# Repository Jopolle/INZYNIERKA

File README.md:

# Repozytorium projektu inżynierskiego

W repozytorium znajdują się wszystkie istotne pliki dotyczące projektu

- Folder HVAC_STM32F7_PCB zawiera schematy projektowanego PCB jak i projekt samej płytki

- Folder dokumentacja zawiera pliki LaTeX pracy inżynierskiej i ostatnią skompilowaną wersję

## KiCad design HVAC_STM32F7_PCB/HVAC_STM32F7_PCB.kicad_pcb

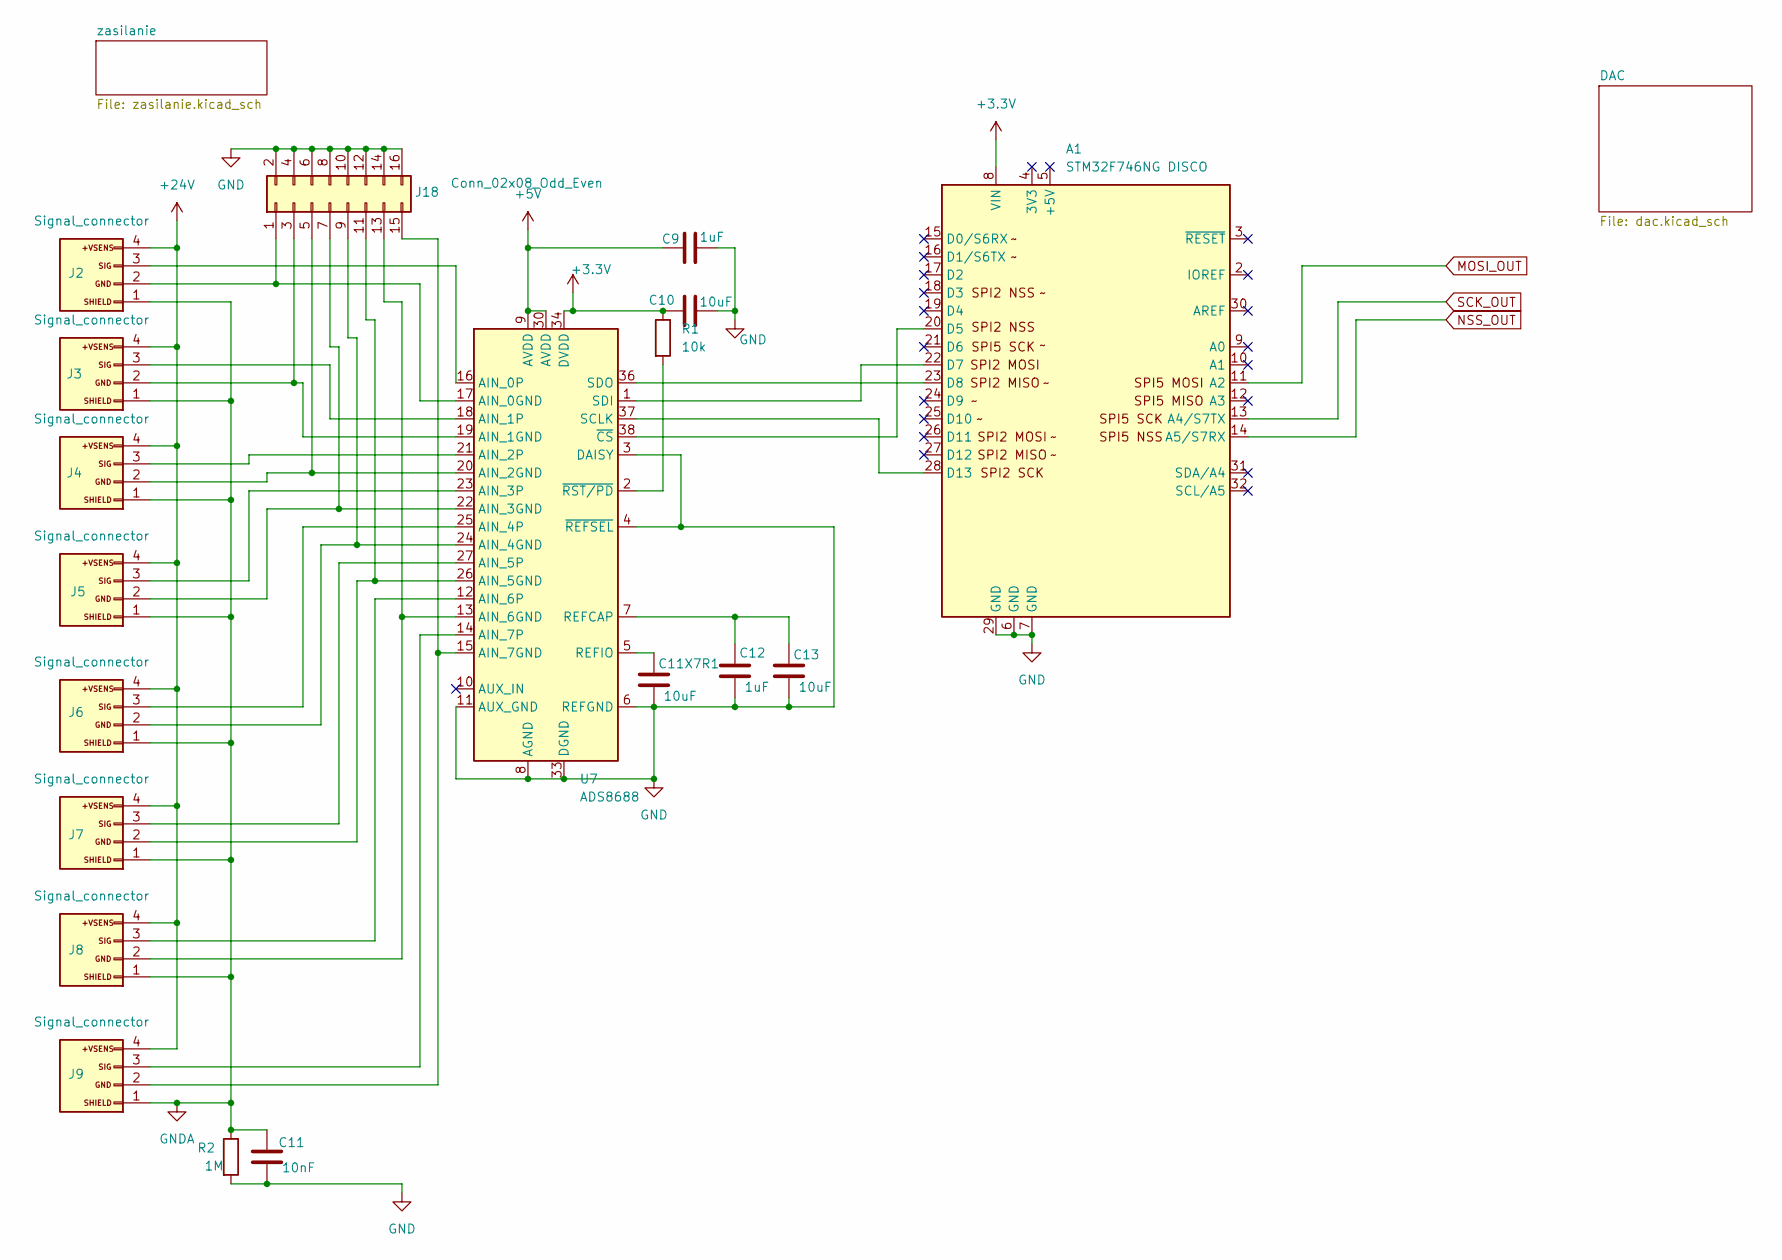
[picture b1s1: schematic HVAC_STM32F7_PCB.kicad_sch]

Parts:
A1: STM32F746NG DISCO; STM32F7_DISCO
C9, C12: 1uF; C_0805_2012Metric_Pad1.18x1.45mm_HandSolder
C10, C11X7R1, C13: 10uF; C_0805_2012Metric_Pad1.18x1.45mm_HandSolder
C11: 10nF; C_0805_2012Metric_Pad1.18x1.45mm_HandSolder
J2, J3, J4, J5, J6, J7, J8, J9: Signal_connector; PhoenixContact_MCV_1,5_4-G-3.5_1x04_P3.50mm_Vertical
J18: Conn_02x08_Odd_Even; PinHeader_2x08_P2.54mm_Vertical
R1: 10k; R_0805_2012Metric_Pad1.20x1.40mm_HandSolder
R2: 1M; R_0805_2012Metric_Pad1.20x1.40mm_HandSolder
U7: ADS8688; TSSOP-38_4.4x9.7mm_P0.5mm

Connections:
+3.3V: A1.8 (VIN), C10.1, R1.1, U7.34 (DVDD); also elsewhere on the board
+5V: C9.2, U7.9 (AVDD), U7.30 (AVDD); also elsewhere on the board
+24V: J2.4 (+VSENS), J3.4 (+VSENS), J4.4 (+VSENS), J5.4 (+VSENS), J6.4 (+VSENS), J7.4 (+VSENS), J8.4 (+VSENS), J9.4 (+VSENS); also elsewhere on the board
GND: A1.6 (GND), A1.7 (GND), A1.29 (GND), C9.1, C10.2, C11.2, C11X7R1.2, C12.2, C13.2, J18.2, J18.4, J18.6, J18.8, J18.10, J18.12, J18.14, J18.16, R2.2, U7.3 (DAISY), U7.4 (~REFSEL), U7.6 (REFGND), U7.8 (AGND), U7.11 (AUX_GND), U7.28 (AGND), U7.29 (AGND), U7.31 (AGND), U7.32 (AGND), U7.33 (DGND); also elsewhere on the board
GNDA: C11.1, J2.1 (SHIELD), J3.1 (SHIELD), J4.1 (SHIELD), J5.1 (SHIELD), J6.1 (SHIELD), J7.1 (SHIELD), J8.1 (SHIELD), J9.1 (SHIELD), R2.1; also elsewhere on the board
MOSI_OUT: A1.11 (A2); also elsewhere on the board
NSS_OUT: A1.14 (A5/S7RX); also elsewhere on the board
unnamed: A1.20 (D5), U7.38 (~CS)
unnamed: A1.22 (D7), U7.1 (SDI)
unnamed: A1.23 (D8), U7.36 (SDO)
unnamed: A1.28 (D13), U7.37 (SCLK)
unnamed: J2.3 (SIG), U7.16 (AIN_0P)
unnamed: J3.3 (SIG), U7.18 (AIN_1P)
unnamed: J4.3 (SIG), U7.21 (AIN_2P)
unnamed: J5.3 (SIG), U7.23 (AIN_3P)
unnamed: J6.3 (SIG), U7.25 (AIN_4P)
unnamed: J7.3 (SIG), U7.27 (AIN_5P)
unnamed: J8.3 (SIG), U7.12 (AIN_6P)
unnamed: J9.3 (SIG), U7.14 (AIN_7P)
unnamed: J2.2 (GND), J18.1, U7.17 (AIN_0GND)
unnamed: J3.2 (GND), J18.3, U7.19 (AIN_1GND)
unnamed: J4.2 (GND), J18.5, U7.20 (AIN_2GND)
unnamed: J5.2 (GND), J18.7, U7.22 (AIN_3GND)
unnamed: J6.2 (GND), J18.9, U7.24 (AIN_4GND)
unnamed: J7.2 (GND), J18.11, U7.26 (AIN_5GND)
unnamed: J8.2 (GND), J18.13, U7.13 (AIN_6GND)
unnamed: J9.2 (GND), J18.15, U7.15 (AIN_7GND)
unnamed: C12.1, C13.1, U7.7 (REFCAP)
unnamed: C11X7R1.1, U7.5 (REFIO)
unnamed: R1.2, U7.2 (~RST/PD)
SCK_OUT: A1.13 (A4/S7TX); also elsewhere on the board

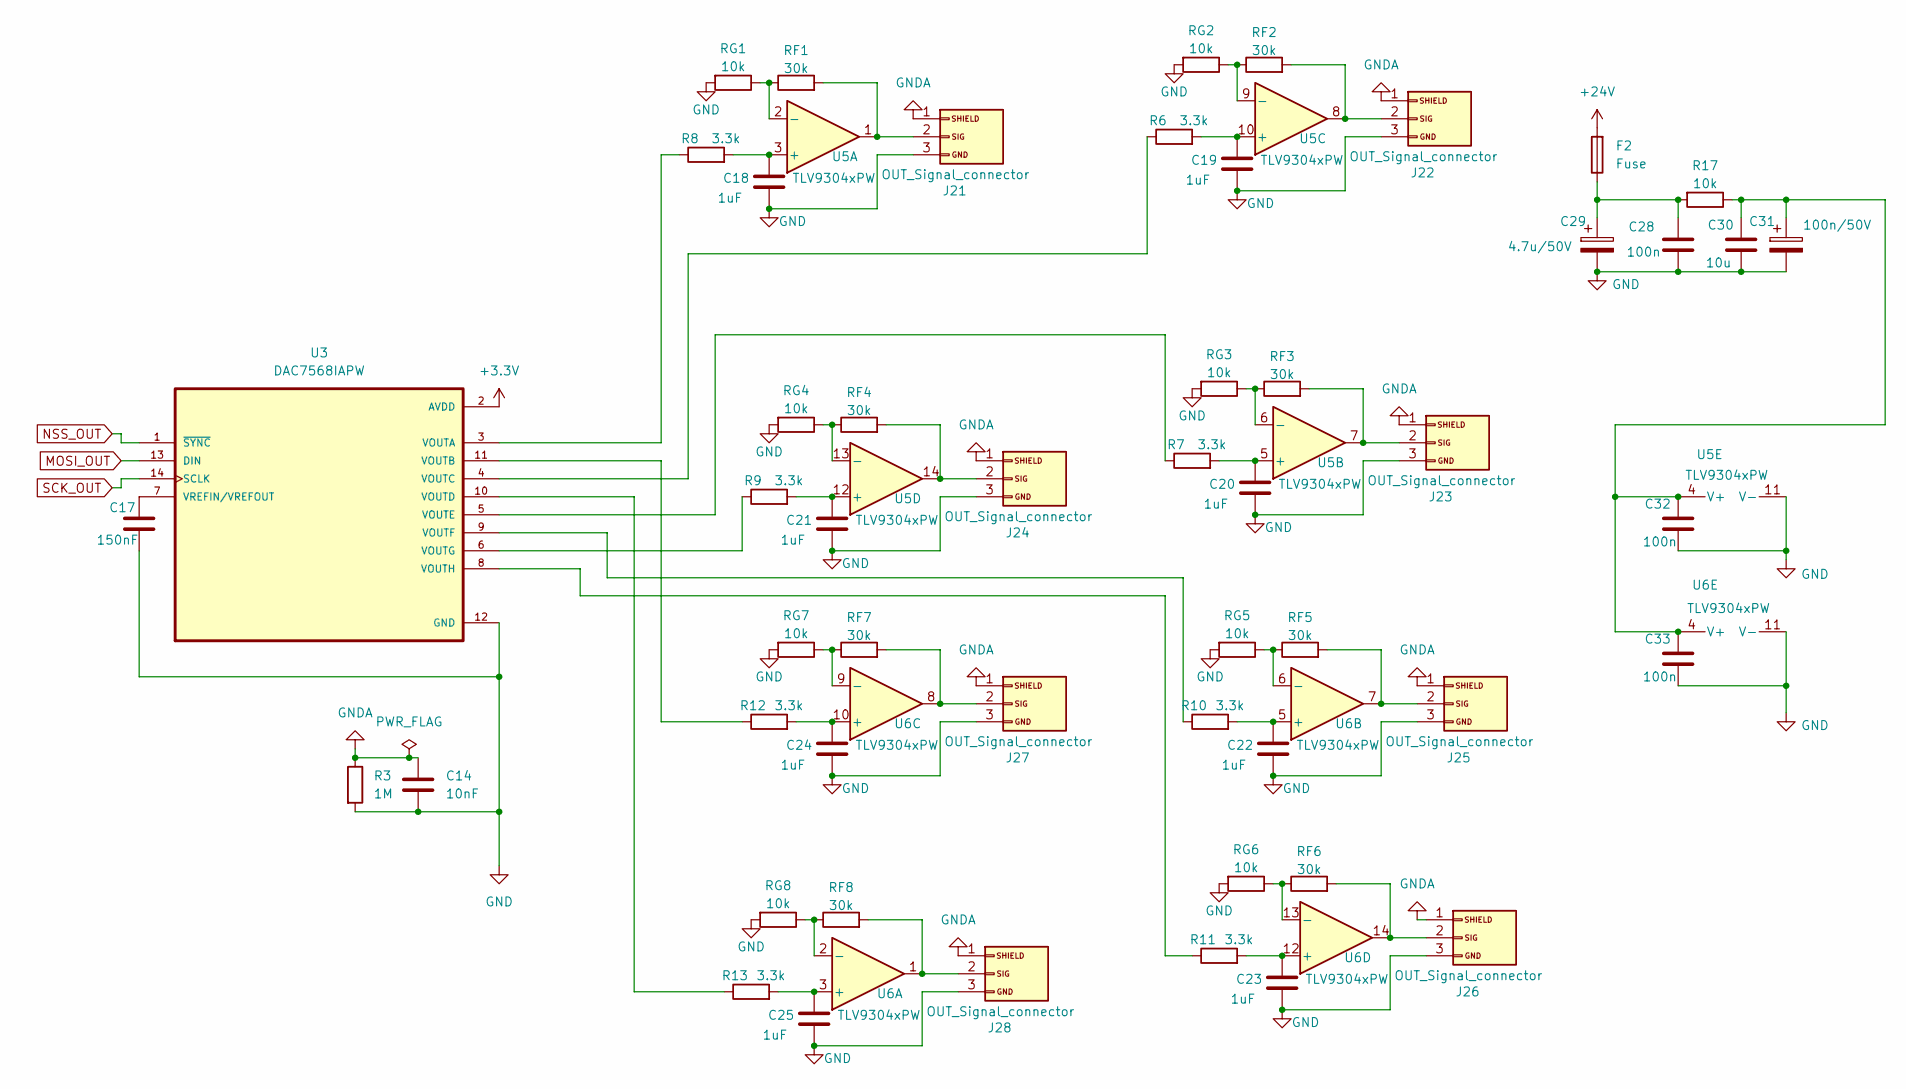
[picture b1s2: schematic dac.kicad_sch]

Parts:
C14: 10nF; C_0805_2012Metric_Pad1.18x1.45mm_HandSolder
C17: 150nF; C_0805_2012Metric_Pad1.18x1.45mm_HandSolder
C18, C19, C20, C21, C22, C23, C24, C25: 1uF; C_0805_2012Metric_Pad1.18x1.45mm_HandSolder
C28, C32, C33: 100n; C_0805_2012Metric_Pad1.18x1.45mm_HandSolder
C29: 4.7u/50V; C_2220_5750Metric_Pad1.97x5.40mm_HandSolder
C30: 10u; C_0805_2012Metric_Pad1.18x1.45mm_HandSolder
C31: 100n/50V; C_0805_2012Metric_Pad1.18x1.45mm_HandSolder
F2: Fuse; Fuse_1812_4532Metric_Pad1.30x3.40mm_HandSolder
J21, J22, J23, J24, J25, J26, J27, J28: OUT_Signal_connector; PhoenixContact_MCV_1,5_3-G-3.5_1x03_P3.50mm_Vertical
R3: 1M; R_0805_2012Metric_Pad1.20x1.40mm_HandSolder
R6, R7, R8, R9, R10, R11, R12, R13: 3.3k; R_0805_2012Metric_Pad1.20x1.40mm_HandSolder
R17: 10k; R_0805_2012Metric_Pad1.20x1.40mm_HandSolder
RF1, RF2, RF3, RF4, RF5, RF6, RF7, RF8: 30k; R_0805_2012Metric_Pad1.20x1.40mm_HandSolder
RG1, RG2, RG3, RG4, RG5, RG6, RG7, RG8: 10k; R_0805_2012Metric_Pad1.20x1.40mm_HandSolder
U3: DAC7568IAPW; dac
U5, U6: TLV9304xPW; TSSOP-14_4.4x5mm_P0.65mm

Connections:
+3.3V: U3.2 (AVDD); also elsewhere on the board
+24V: F2.2; also elsewhere on the board
GND: C14.2, C17.2, C18.2, C19.2, C20.2, C21.2, C22.2, C23.2, C24.2, C25.2, C28.2, C29.2, C30.2, C31.2, C32.2, C33.2, J21.3 (SIG), J22.3 (SIG), J23.3 (SIG), J24.3 (SIG), J25.3 (SIG), J26.3 (SIG), J27.3 (SIG), J28.3 (SIG), R3.2, RG1.2, RG2.2, RG3.2, RG4.2, RG5.2, RG6.2, RG7.2, RG8.2, U3.12 (GND), U5.11 (V-), U6.11 (V-); also elsewhere on the board
GNDA: C14.1, J21.1 (SHIELD), J22.1 (SHIELD), J23.1 (SHIELD), J24.1 (SHIELD), J25.1 (SHIELD), J26.1 (SHIELD), J27.1 (SHIELD), J28.1 (SHIELD), R3.1; also elsewhere on the board
MOSI_OUT: U3.13 (DIN); also elsewhere on the board
NSS_OUT: U3.1 (~SYNC); also elsewhere on the board
unnamed: C28.1, C29.1, F2.1, R17.2
unnamed: J21.2 (GND), RF1.2, U5.1
unnamed: J22.2 (GND), RF2.2, U5.8
unnamed: J23.2 (GND), RF3.2, U5.7
unnamed: J24.2 (GND), RF4.2, U5.14
unnamed: J25.2 (GND), RF5.2, U6.7
unnamed: J26.2 (GND), RF6.2, U6.14
unnamed: J27.2 (GND), RF7.2, U6.8
unnamed: J28.2 (GND), RF8.2, U6.1
unnamed: R8.1, U3.3 (VOUTA)
unnamed: R12.1, U3.11 (VOUTB)
unnamed: R6.1, U3.4 (VOUTC)
unnamed: R13.1, U3.10 (VOUTD)
unnamed: R7.1, U3.5 (VOUTE)
unnamed: R10.1, U3.9 (VOUTF)
unnamed: R9.1, U3.6 (VOUTG)
unnamed: R11.1, U3.8 (VOUTH)
unnamed: C17.1, U3.7 (VREFIN/VREFOUT)
unnamed: C18.1, R8.2, U5.3 (+)
unnamed: RF1.1, RG1.1, U5.2 (-)
unnamed: C20.1, R7.2, U5.5 (+)
unnamed: RF3.1, RG3.1, U5.6 (-)
unnamed: C19.1, R6.2, U5.10 (+)
unnamed: RF2.1, RG2.1, U5.9 (-)
unnamed: C21.1, R9.2, U5.12 (+)
unnamed: RF4.1, RG4.1, U5.13 (-)
unnamed: C30.1, C31.1, C32.1, C33.1, R17.1, U5.4 (V+), U6.4 (V+)
unnamed: C25.1, R13.2, U6.3 (+)
unnamed: RF8.1, RG8.1, U6.2 (-)
unnamed: C22.1, R10.2, U6.5 (+)
unnamed: RF5.1, RG5.1, U6.6 (-)
unnamed: C24.1, R12.2, U6.10 (+)
unnamed: RF7.1, RG7.1, U6.9 (-)
unnamed: C23.1, R11.2, U6.12 (+)
unnamed: RF6.1, RG6.1, U6.13 (-)
SCK_OUT: U3.14 (SCLK); also elsewhere on the board

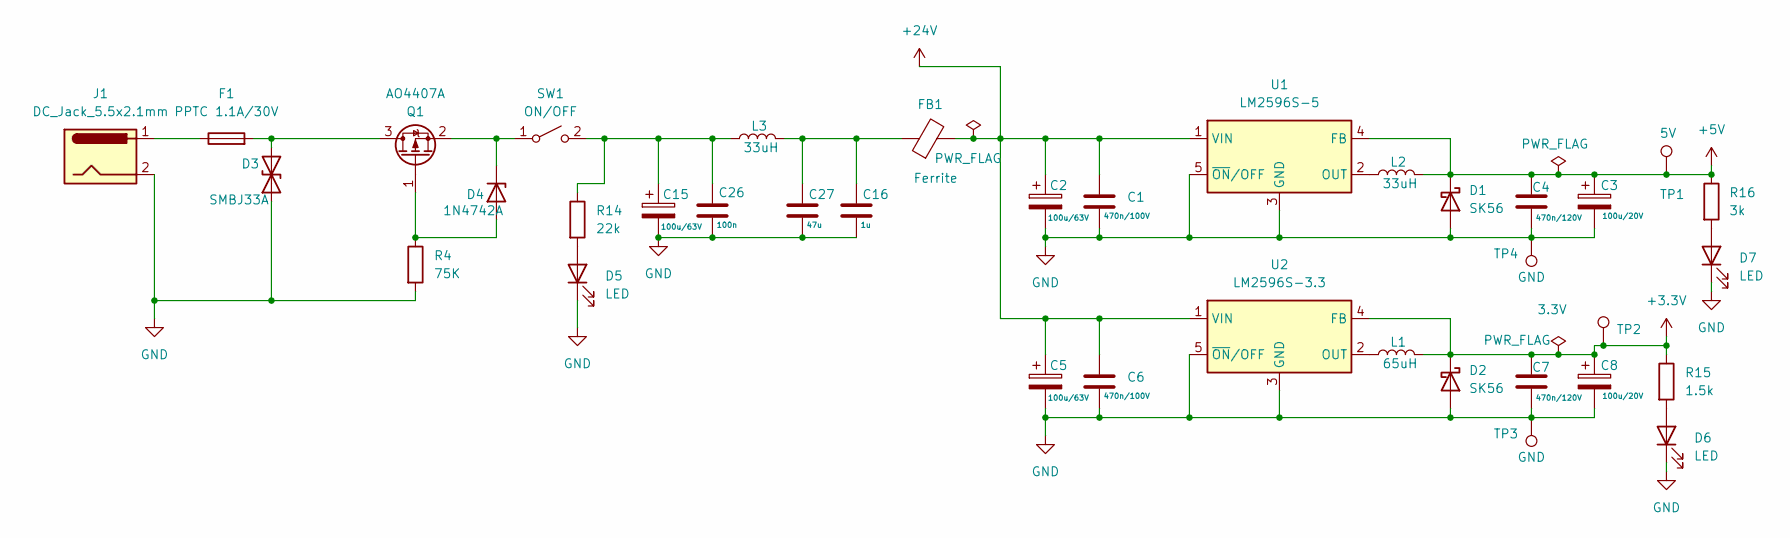
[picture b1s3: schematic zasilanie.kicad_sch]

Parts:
C1, C6: 470n/100V; C_1808_4520Metric_Pad1.72x2.30mm_HandSolder
C2, C5, C15: 100u/63V; CP_Radial_D8.0mm_P3.80mm
C3, C8: 100u/20V; CP_Radial_D8.0mm_P3.80mm
C4, C7: 470n/120V; C_1808_4520Metric_Pad1.72x2.30mm_HandSolder
C16: 1u; C_1808_4520Metric_Pad1.72x2.30mm_HandSolder
C26: 100n; C_1808_4520Metric_Pad1.72x2.30mm_HandSolder
C27: 47u; C_1808_4520Metric_Pad1.72x2.30mm_HandSolder
D1, D2: SK56; D_SMB-SMC_Universal_Handsoldering
D3: SMBJ33A; D_SMB_Handsoldering
D4: 1N4742A; D_DO-41_SOD81_P2.54mm_Vertical_AnodeUp
D5, D6, D7: LED; LED_D5.0mm_Clear
F1: PPTC 1.1A/30V; Fuseholder_Blade_Mini_Keystone_3568
FB1: Ferrite; L_1210_3225Metric_Pad1.42x2.65mm_HandSolder
J1: DC_Jack_5.5x2.1mm; BarrelJack_Horizontal
L1: 65uH; L_12x12mm_H4.5mm
L2, L3: 33uH; L_6.3x6.3_H3
Q1: AO4407A; PowerPAK_SO-8_Single
R4: 75K; R_0805_2012Metric_Pad1.20x1.40mm_HandSolder
R14: 22k; R_0805_2012Metric_Pad1.20x1.40mm_HandSolder
R15: 1.5k; R_0805_2012Metric_Pad1.20x1.40mm_HandSolder
R16: 3k; R_0805_2012Metric_Pad1.20x1.40mm_HandSolder
SW1: ON/OFF; SLW-1276864-4A-D_FOOTPRINT
TP1: 5V; TestPoint_Loop_D1.80mm_Drill1.0mm_Beaded
TP2: 3.3V; TestPoint_Loop_D1.80mm_Drill1.0mm_Beaded
TP3, TP4: GND; TestPoint_Loop_D1.80mm_Drill1.0mm_Beaded
U1: LM2596S-5; TO-263-5_TabPin3
U2: LM2596S-3.3; TO-263-5_TabPin3

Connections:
+3.3V: C7.1, C8.1, D2.1 (K), L1.2, R15.1, TP2.1, U2.4 (FB); also elsewhere on the board
+5V: C3.1, C4.1, D1.1 (K), L2.2, R16.1, TP1.1, U1.4 (FB); also elsewhere on the board
+24V: C1.1, C2.1, C5.1, C6.1, FB1.2, U1.1 (VIN), U2.1 (VIN); also elsewhere on the board
GND: C1.2, C2.2, C3.2, C4.2, C5.2, C6.2, C7.2, C8.2, C15.2, C16.2, C26.2, C27.2, D1.2 (A), D2.2 (A), D3.1 (A1), D5.1 (K), D6.1 (K), D7.1 (K), J1.2, R4.2, TP3.1, TP4.1, U1.3 (GND), U1.5 (~ON/OFF), U2.3 (GND), U2.5 (~ON/OFF); also elsewhere on the board
unnamed: C16.1, C27.1, FB1.1, L3.2
unnamed: D3.2 (A2), F1.2, Q1.3 (D)
unnamed: D4.2 (A), Q1.1 (G), R4.1
unnamed: D4.1 (K), Q1.2 (S), SW1.1 (A)
unnamed: D5.2 (A), R14.2
unnamed: D6.2 (A), R15.2
unnamed: D7.2 (A), R16.2
unnamed: F1.1, J1.1
unnamed: C15.1, C26.1, L3.1, R14.1, SW1.2 (B)
unnamed: L2.1, U1.2 (OUT)
unnamed: L1.1, U2.2 (OUT)

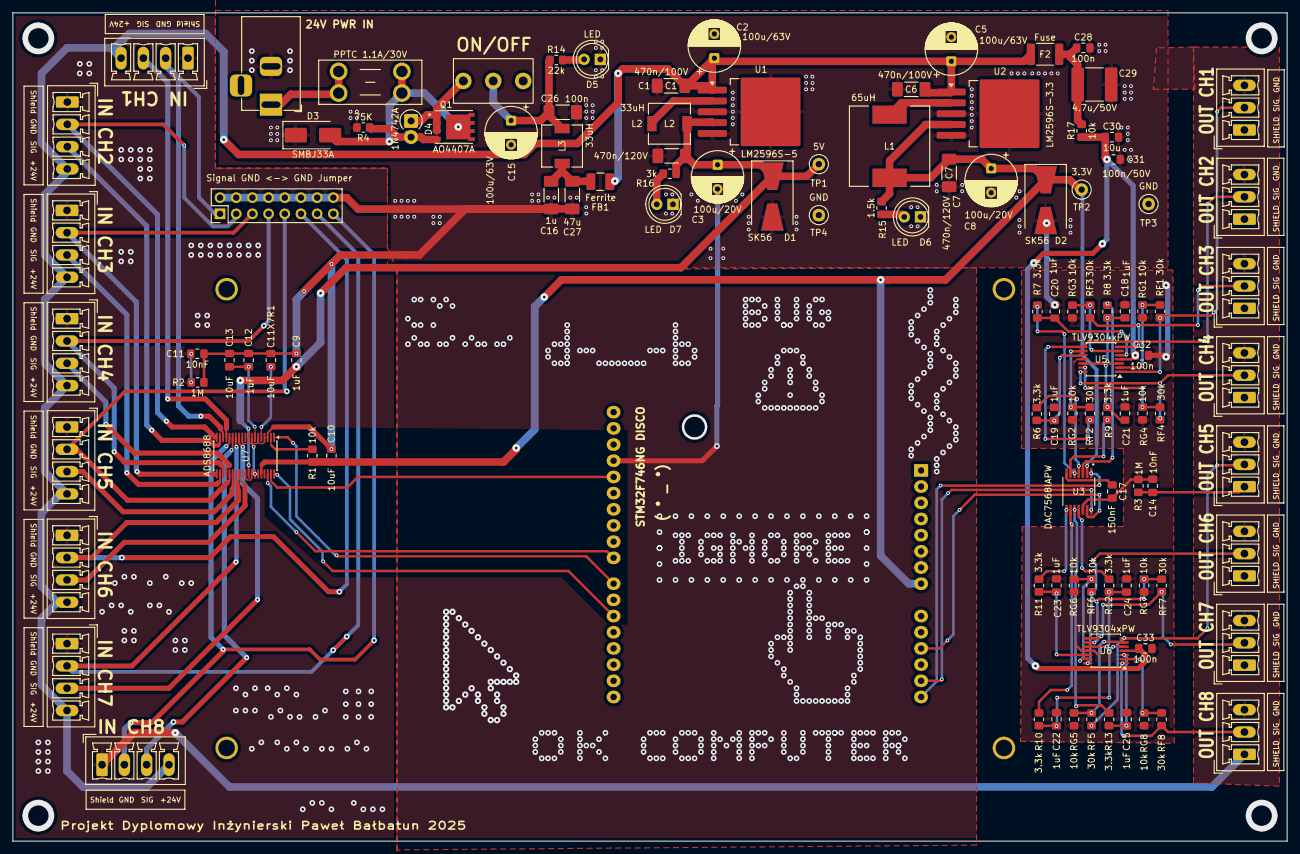
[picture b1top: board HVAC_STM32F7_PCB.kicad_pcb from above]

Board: 4 copper layers, 200.0 x 130.0 mm, 110 parts (0 on the bottom side), 77 nets.

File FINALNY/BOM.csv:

"Value","Footprint","Qty","Reference","DNP","Exclude from BOM","Exclude from Board","Datasheet"
"470n/100V","Capacitor_SMD:C_1808_4520Metric_Pad1.72x2.30mm_HandSolder","2","C1,C6","","","","~"
"100u/63V","Capacitor_THT:CP_Radial_D8.0mm_P3.80mm","3","C2,C5,C15","","","","~"
"100u/20V","Capacitor_THT:CP_Radial_D8.0mm_P3.80mm","2","C3,C8","","","","~"
"470n/120V","Capacitor_SMD:C_1808_4520Metric_Pad1.72x2.30mm_HandSolder","2","C4,C7","","","","~"
"1uF","Capacitor_SMD:C_0805_2012Metric_Pad1.18x1.45mm_HandSolder","10","C9,C12,C18,C19,C20,C21,C22,C23,C24,C25","","","","~"
"10uF","Capacitor_SMD:C_0805_2012Metric_Pad1.18x1.45mm_HandSolder","3","C10,C11X7R1,C13","","","","~"
"10nF","Capacitor_SMD:C_0805_2012Metric_Pad1.18x1.45mm_HandSolder","2","C11,C14","","","","~"
"1u","Capacitor_SMD:C_1808_4520Metric_Pad1.72x2.30mm_HandSolder","1","C16","","","","~"
"150nF","Capacitor_SMD:C_0805_2012Metric_Pad1.18x1.45mm_HandSolder","1","C17","","","","~"
"100n","Capacitor_SMD:C_1808_4520Metric_Pad1.72x2.30mm_HandSolder","1","C26","","","","~"
"47u","Capacitor_SMD:C_1808_4520Metric_Pad1.72x2.30mm_HandSolder","1","C27","","","","~"
"100n","Capacitor_SMD:C_0805_2012Metric_Pad1.18x1.45mm_HandSolder","3","C28,C32,C33","","","","~"
"4.7u/50V","Capacitor_SMD:C_2220_5750Metric_Pad1.97x5.40mm_HandSolder","1","C29","","","","~"
"10u","Capacitor_SMD:C_0805_2012Metric_Pad1.18x1.45mm_HandSolder","1","C30","","","","~"
"100n/50V","Capacitor_SMD:C_0805_2012Metric_Pad1.18x1.45mm_HandSolder","1","C31","","","","~"
"SK56","Diode_SMD:D_SMB-SMC_Universal_Handsoldering","2","D1,D2","","","","~"
"SMBJ33A","Diode_SMD:D_SMB_Handsoldering","1","D3","","","","~"
"1N4742A","Diode_THT:D_DO-41_SOD81_P2.54mm_Vertical_AnodeUp","1","D4","","","","~"
"LED","LED_THT:LED_D5.0mm_Clear","3","D5,D6,D7","","","","~"
"PPTC 1.1A/30V","Fuse:Fuseholder_Blade_Mini_Keystone_3568","1","F1","","","","~"
"Fuse","Fuse:Fuse_1812_4532Metric_Pad1.30x3.40mm_HandSolder","1","F2","","","","~"
"Ferrite","Inductor_SMD:L_1210_3225Metric_Pad1.42x2.65mm_HandSolder","1","FB1","","","","~"
"DC_Jack_5.5x2.1mm","Connector_BarrelJack:BarrelJack_Horizontal","1","J1","","","","~"
"Signal_connector","Connector_Phoenix_MC:PhoenixContact_MCV_1,5_4-G-3.5_1x04_P3.50mm_Vertical","8","J2,J3,J4,J5,J6,J7,J8,J9","","","","~"
"Conn_02x08_Odd_Even","Connector_PinHeader_2.54mm:PinHeader_2x08_P2.54mm_Vertical","1","J18","","","","~"
"OUT_Signal_connector","Connector_Phoenix_MC:PhoenixContact_MCV_1,5_3-G-3.5_1x03_P3.50mm_Vertical","8","J21,J22,J23,J24,J25,J26,J27,J28","","","","~"
"65uH","Inductor_SMD:L_12x12mm_H4.5mm","1","L1","","","","Epcos 871-PID120HS-650M"
"33uH","Inductor_SMD:L_6.3x6.3_H3","2","L2,L3","","","","Power Inductors - SMD Ind,6.8x6.8x3.8mm,33uH+/-20%,1.35A,"
"AO4407A","własne:PowerPAK_SO-8_Single","1","Q1","","","","~"
"10k","Resistor_SMD:R_0805_2012Metric_Pad1.20x1.40mm_HandSolder","10","R1,R17,RG1,RG2,RG3,RG4,RG5,RG6,RG7,RG8","","","","~"
"1M","Resistor_SMD:R_0805_2012Metric_Pad1.20x1.40mm_HandSolder","2","R2,R3","","","","~"
"75K","Resistor_SMD:R_0805_2012Metric_Pad1.20x1.40mm_HandSolder","1","R4","","","","~"
"3.3k","Resistor_SMD:R_0805_2012Metric_Pad1.20x1.40mm_HandSolder","8","R6,R7,R8,R9,R10,R11,R12,R13","","","","~"
"22k","Resistor_SMD:R_0805_2012Metric_Pad1.20x1.40mm_HandSolder","1","R14","","","","~"
"1.5k","Resistor_SMD:R_0805_2012Metric_Pad1.20x1.40mm_HandSolder","1","R15","","","","~"
"3k","Resistor_SMD:R_0805_2012Metric_Pad1.20x1.40mm_HandSolder","1","R16","","","","~"
"30k","Resistor_SMD:R_0805_2012Metric_Pad1.20x1.40mm_HandSolder","8","RF1,RF2,RF3,RF4,RF5,RF6,RF7,RF8","","","","~"
"ON/OFF","slide_switches:SLW-1276864-4A-D_FOOTPRINT","1","SW1","","","","~"
"5V","TestPoint:TestPoint_Loop_D1.80mm_Drill1.0mm_Beaded","1","TP1","","","",""
"3.3V","TestPoint:TestPoint_Loop_D1.80mm_Drill1.0mm_Beaded","1","TP2","","","","~"
"GND","TestPoint:TestPoint_Loop_D1.80mm_Drill1.0mm_Beaded","2","TP3,TP4","","","","~"
"LM2596S-5","Package_TO_SOT_SMD:TO-263-5_TabPin3","1","U1","","","","http://www.ti.com/lit/ds/symlink/lm2596.pdf"
"LM2596S-3.3","Package_TO_SOT_SMD:TO-263-5_TabPin3","1","U2","","","","http://www.ti.com/lit/ds/symlink/lm2596.pdf"
"DAC7568IAPW","własne:dac","1","U3","","","",""
"TLV9304xPW","Package_SO:TSSOP-14_4.4x5mm_P0.65mm","2","U5,U6","","","","https://www.ti.com/lit/ds/symlink/tlv9304.pdf"
"ADS8688","Package_SO:TSSOP-38_4.4x9.7mm_P0.5mm","1","U7","","","","http://www.ti.com/lit/ds/symlink/ads8688.pdf"
"STM32F746NG DISCO","własne:STM32F7_DISCO","1","A1","","Excluded from BOM","","https://www.arduino.cc/en/Main/arduinoBoardUno"

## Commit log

2025-10-09 Add REAMDE
2025-10-09 initial document compile
2025-10-14 ADD: c-l-c filter, PMOS controll, inditacor LEDs, JLCPCB technology capabilities TODO: footprint assignment to lacking elements,
2025-10-14 ADD: working first draft compilation of documentation, PCB project playing around
2025-10-14 ADD: PCB design started, power supply, buck converters and input ADC placed
2025-10-16 add power and input signal trace
2025-10-17 ADD finished pcb traces
2025-10-19 add: schematic and pcb pdf to view
2025-10-19 ADD: Wstęp do przeglądu hardware'u, dokładny opis modułu zasilającego
2025-10-21 ADD: małe poprawki do sekcji z modułem zasilania, dodana sekcja z torem wyjściowym
2025-10-27 add: mostly finished hardware section, dywagacje nad wyborem oprogramowanioa
2025-10-28 ADD: walka z przestawianiem konektorów wejściowych i wyjściowych, TODO: dokończyć łączenie wejściowego ADC
2025-10-29 add: ADC podłączone elegancko, separacja mas sygnałów wejściowych, TODO: DRC
2025-11-03 ADD: poprawki w tekscie pracy, cytowania,
2025-11-04 fix: drc, TODO thicker tracks
2025-11-06 zabawy z grubościami ścierzek
2025-11-06 ADD naprawione DRC, TODO last check, filkscreen text
2025-11-07 ADD kosmetyka większości opisów komponenów, TODO: ogarnąć masę zasilania aktywnych czujników
2025-11-11 poprawki zmiana maszyny
2025-11-12 kontynuacja walki z pcb
2025-11-18 ADD Poprawki PCB layout TODO zasilanie toru wyjciowego, podpisy elementow i kosmetyka
2025-11-19 ADD final pcb version for review, god bless
2025-11-19 ADD pierwsza wersja uruchomienia lvgl poprawnie TODO update do rozbudowanej wersji
2025-11-21 ADD poprawki w tekście i formatowaniu
2025-11-23 ADD: nowe ekrany LVGL, działająca konfiguarcja- quicksave przed overhaulem
2025-11-23 ADD: update remote repo
2025-11-25 ADD: próby połączenia LVGL z obsługą karty SD -> poddanie się -> budowanie GUI na nowo
2025-11-25 ADD: proste wgrywaine konfiguracji z string TODO: rozszerzenie konfiguracji o sekwencje grzania/chłodzenia i mapowanie I/O
2025-11-26 ADD: działający kontroler z regulatorem PID woooooooo TODO: symulacja on board
2025-11-28 ADD hopefully finished pcb project
2025-11-29 ADD: opis części hardware, dodane zdjęcia i schematy
2025-12-02 ADD: poprawki pcb, nowe gerbery
2025-12-02 ADD: opis stanu wiedzy, początki zabawy z opisem firmware
2025-12-04 ADD: wgranie ikonek, poprawa parsowania konfiguracji, wizualne zmiany dla bajeranckości, TBA: ekran wglądu sekwencji odzysku ciepła, ikonki dla kanałów I/O
2025-12-04 ADD: wzmianka o uwspólnianiu masy, punkty testowe i poprawy formatowania
2025-12-05 ADD: tekst części firmware, rozwinięcie wymagań i założeń projektu rozbudowa bibliografii TODO: zdjęcia i odniesienia firmware, próba zaprogramowania dynamicznych wykresów sekwencji
2025-12-07 ADD: poprawki od promotora v1
2025-12-08 ADD: działający ekran sequence visualiser, updateowany wraz ze zmianą wyglądu ze zmianą zakresów
2025-12-09 ADD: zdjecia GUI, rework sekcji kierunków rozwoju, dodanie opisu tlv, wstowiony render płytki
2025-12-09 ADD: opis skrótów, rework kierunków rozwoju firmware
2025-12-10 ADD: finalne zmiany, wysyłanie dokumentu do recenzji
